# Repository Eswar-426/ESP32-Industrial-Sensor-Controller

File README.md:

# ESP32 Industrial Sensor Controller

A custom, compact PCB designed in **KiCad 10** for an ESP32-based industrial temperature and humidity monitoring system.

The board integrates an **ESP32-WROOM-32** Wi-Fi & Bluetooth microcontroller module, a high-precision **Sensirion SHT31-DIS** digital environmental sensor, and an ultra-low-dropout **AP2112K-3.3** voltage regulator. It features dedicated I²C bus pull-up resistors, hardware Reset and Boot mode tactile switches, comprehensive decoupling networks, and an FTDI-compatible 6-pin UART interface for flashing and serial telemetry.

---

## 3D Board Visualization

<p align="center">
  
  &nbsp;
  
</p>

---

## Features

- **Microcontroller Core:** Espressif ESP32-WROOM-32 dual-core Tensilica Xtensa 32-bit LX6 processor with 2.4 GHz Wi-Fi (802.11 b/g/n) and Bluetooth v4.2 BR/EDR & BLE.
- **Precision Environmental Sensing:** Sensirion SHT31-DIS digital sensor connected via I²C bus (`IO21` SDA, `IO22` SCL) providing ±2% RH accuracy and ±0.2 °C temperature accuracy.
- **Power Management:** AP2112K-3.3 high-current (600 mA), low-noise, ultra-low dropout (LDO) linear regulator delivering stable 3.3 V with dedicated input and output decoupling.
- **Programming & Serial Telemetry:** 6-pin 2.54 mm pitch UART programming header with direct connections to ESP32 UART0 (`TXD0`/`RXD0`), power rails, reset line (`EN`), and boot line (`IO0`).
- **Tactile User Controls:** Dedicated tactile buttons for hardware Reset (`SW1`, EN to GND) and Boot Mode configuration (`SW2`, IO0 to GND) with external 10 kΩ pull-ups.
- **Robust Signal & Power Integrity:** 2-layer PCB stackup with continuous front (F.Cu) and back (B.Cu) ground copper pours, low-inductance thermal via stitching, and dedicated 0603 decoupling capacitors per IC.
- **Antenna Keepout Compliance:** Clean PCB cutout/keepout area maintained around the ESP32 onboard PCB trace antenna to preserve RF performance.

---

## Schematic Overview

*Complete schematic available in vector format: [docs/schematic.pdf](docs/schematic.pdf).*

---

## Bill of Materials (BOM)

| Reference | Value / Part | Package / Footprint | Description | Qty |
| :--- | :--- | :--- | :--- | :---: |
| **U1** | `AP2112K-3.3` | SOT-23-5 | 600 mA Low-Dropout Linear Voltage Regulator (5V to 3.3V) | 1 |
| **U2** | `ESP32-WROOM-32` | SMD-38 (18×25.5 mm) | Espressif Dual-Core Wi-Fi & BLE Microcontroller Module | 1 |
| **U3** | `SHT31-DIS` | DFN-8 (2.5×2.5 mm) | Sensirion High-Precision Digital Humidity & Temperature Sensor | 1 |
| **C1, C2** | `1 µF` | 0603 SMD | Input & Output Filter Capacitors for AP2112K LDO | 2 |
| **C3** | `10 µF` | 0603 SMD | Bulk Decoupling Capacitor for ESP32 3V3 Rail | 1 |
| **C4, C5** | `100 nF` | 0603 SMD | High-Frequency Bypass / Decoupling Capacitors (ESP32 & SHT31) | 2 |
| **R2, R3** | `10 kΩ` | 0603 SMD | Pull-Up Resistors for Boot (`IO0`) and Reset (`EN`) Lines | 2 |
| **R4, R5** | `4.7 kΩ` | 0603 SMD | Dedicated Pull-Up Resistors for I²C Bus (`SDA`, `SCL`) | 2 |
| **SW1, SW2** | `SPST Push Button` | SMD (KMS2xxGP) | Reset (`EN`) and Boot (`IO0`) Control Switches | 2 |
| **J1** | `6-Pin Header (1x06)`| PinHeader 2.54 mm Vertical | UART Interface for Flashing, Debugging & Power Input | 1 |

*Machine-readable CSV format: [docs/bom.csv](docs/bom.csv).*

---

## Pinout & Interface Mapping

### Programming Header (J1)

| Pin | Net Name | Target Device / Pin | Function / Usage |
| :---: | :---: | :---: | :--- |
| **1** | `GND` | System Ground Plane | Common ground connection |
| **2** | `+3.3V` | System 3.3 V Power Rail | 3.3 V supply rail / power monitor |
| **3** | `RXD0` | ESP32 `RXD0` (`GPIO3`) | Serial receive from external USB-UART programmer (TX) |
| **4** | `TXD0` | ESP32 `TXD0` (`GPIO1`) | Serial transmit to external USB-UART programmer (RX) |
| **5** | `EN` | ESP32 `EN` (Chip Enable) | Hardware reset control (active low) |
| **6** | `IO0` | ESP32 `GPIO0` (Boot) | Flashing bootloader entry (pull low during reset) |

### Internal Sensor Bus (I²C)

| Sensor Pin | Net Name | ESP32 Pin | Function |
| :---: | :---: | :---: | :--- |
| **Pin 1 (SDA)** | `IO21` | `GPIO21` | I²C Serial Data (pulled up by R4: 4.7 kΩ to 3.3V) |
| **Pin 4 (SCL)** | `IO22` | `GPIO22` | I²C Serial Clock (pulled up by R5: 4.7 kΩ to 3.3V) |

---

## Design Tools & Verification

### Design Suite
- **KiCad Version:** 10.0.7
- **Schematic Capture:** KiCad Eeschema
- **Layout & Routing:** KiCad PCB Editor
- **Verification Engine:** KiCad Electrical Rules Checker (ERC) & Design Rules Checker (DRC)

### Verification Methodology & Results
- **Schematic ERC:** Passed with **0 errors and 0 warnings**. Power flags, pin types, and hierarchical nets verified. See [docs/erc-report.rpt](docs/erc-report.rpt).
- **PCB DRC:** The report shows zero violations and zero unconnected items under the current project-specific constraints. The settings include a 0.20 mm minimum through-hole drill and a 0.175 mm minimum hole clearance. These settings do not guarantee manufacturer acceptance or fabrication readiness. Review the switch footprint clearances and confirm the design rules with the selected manufacturer before fabrication. See [docs/drc-report.rpt](docs/drc-report.rpt).
- **Copper Architecture:** Solid ground polygon pours on both Top (F.Cu) and Bottom (B.Cu) layers, interconnected with stitching vias for thermal relief and return path continuity.
- **RF Best Practices:** Antenna trace area isolated from underlying copper planes and external routing traces to ensure signal integrity.

> **Verification Scope Notice:**  
> The hardware design has been fully verified using KiCad's Electrical Rules Check (ERC) and PCB Design Rules Check (DRC). Physical board fabrication, component assembly, firmware flashing, and hardware bench testing have not yet been performed. Fabrication constraints must be re-checked against specific manufacturer design capabilities (e.g., JLCPCB, PCBWay) prior to ordering production panels.

---

## Repository Structure

```
ESP32-Industrial-Sensor-Controller/
├── README.md                                      # Project overview, schematics, BOM, and pinout
├── .gitignore                                     # KiCad lock, backup, and local cache filters
├── hardware/
│   ├── ESP32_Industrial_Sensor_Controller.kicad_pro  # KiCad 10 project file
│   ├── ESP32_Industrial_Sensor_Controller.kicad_sch  # Complete schematic file
│   └── ESP32_Industrial_Sensor_Controller.kicad_pcb  # Fully routed PCB layout
└── docs/
    ├── schematic.pdf                              # Printable vector schematic
    ├── schematic.png                              # High-resolution schematic diagram
    ├── pcb-3d.png                                 # High-definition 3D raytraced board render
    ├── pcb-front.png                              # 3D top render
    ├── pcb-back.png                               # 3D bottom render
    ├── bom.csv                                    # Detailed Bill of Materials
    ├── drc-report.rpt                             # KiCad PCB DRC report (0 errors)
    └── erc-report.rpt                             # KiCad Schematic ERC report (0 errors)
```

---

## Future Improvements & Roadmap

- [ ] Order prototype batch from PCB manufacturer (e.g., JLCPCB / PCBWay) with stencil.
- [ ] Surface-mount component soldering & hot-air rework validation.
- [ ] Power supply rail validation under dynamic RF load (3.3 V line ripple and thermal dissipation).
- [ ] ESP-IDF / Arduino C++ firmware development:
  - SHT31 driver implementation with periodic temperature and relative humidity polling.
  - Non-volatile storage (NVS) Wi-Fi credential provisioning.
  - MQTT / HTTP telemetry publishing to cloud/local IoT dashboards (Home Assistant, AWS IoT, or ThingsBoard).
  - ESP32 Deep Sleep power optimization.
- [ ] Enclosure design (3D printed industrial DIN-rail or wall-mount enclosure).

---

## Project Status

**PCB Design Completed** — Prototype fabrication and hardware validation pending.

---

## Author

**Kanchi Eswar Ram kumar** ([@Eswar-426](https://github.com/Eswar-426))  
ECE Undergraduate | Class of 2026  
*Developed as a PCB design and embedded systems portfolio project.*

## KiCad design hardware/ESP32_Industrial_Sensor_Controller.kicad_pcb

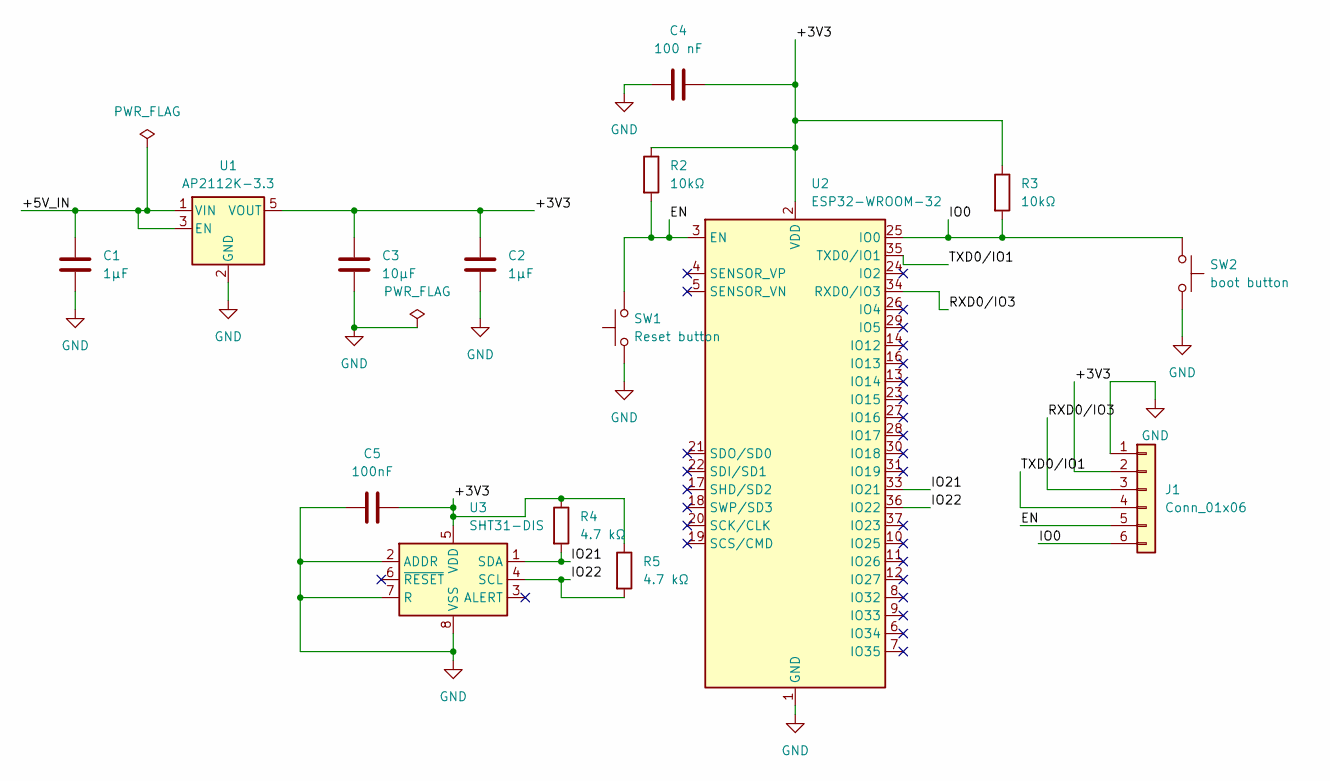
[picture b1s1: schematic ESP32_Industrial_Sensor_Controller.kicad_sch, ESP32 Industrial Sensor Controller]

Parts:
C1, C2: 1µF; C_0603_1608Metric
C3: 10µF; C_0603_1608Metric
C4: 100 nF; C_0603_1608Metric
C5: 100nF; C_0603_1608Metric
J1: Conn_01x06; PinHeader_1x06_P2.54mm_Vertical
R2, R3: 10kΩ; R_0603_1608Metric
R4, R5: 4.7 kΩ; R_0603_1608Metric
SW1: Reset button; SW_SPST_CK_KMS2xxGP
SW2: boot button; SW_SPST_CK_KMS2xxGP
U1: AP2112K-3.3; SOT-23-5
U2: ESP32-WROOM-32
U3: SHT31-DIS; Sensirion_DFN-8-1EP_2.5x2.5mm_P0.5mm_EP1.1x1.7mm

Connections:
/+3V3: C2.1, C3.1, C4.2, C5.2, J1.2, R2.1, R3.1, R4.1, R5.1, U1.5 (VOUT), U2.2 (VDD), U3.5 (VDD)
/+5V_IN: C1.1, U1.1 (VIN), U1.3 (EN)
/EN: J1.5, R2.2, SW1.2, U2.3 (EN)
/IO0: J1.6, R3.2, SW2.1, U2.25 (IO0)
/IO21: R4.2, U2.33 (IO21), U3.1 (SDA)
/IO22: R5.2, U2.36 (IO22), U3.4 (SCL)
/RXD0/IO3: J1.3, U2.34 (RXD0/IO3)
/TXD0/IO1: J1.4, U2.35 (TXD0/IO1)
GND: C1.2, C2.2, C3.2, C4.1, C5.1, J1.1, SW1.1, SW2.2, U1.2 (GND), U2.1 (GND), U2.15 (GND), U2.38 (GND), U2.39 (GND), U3.2 (ADDR), U3.7 (R), U3.8 (VSS), U3.9 (VSS)

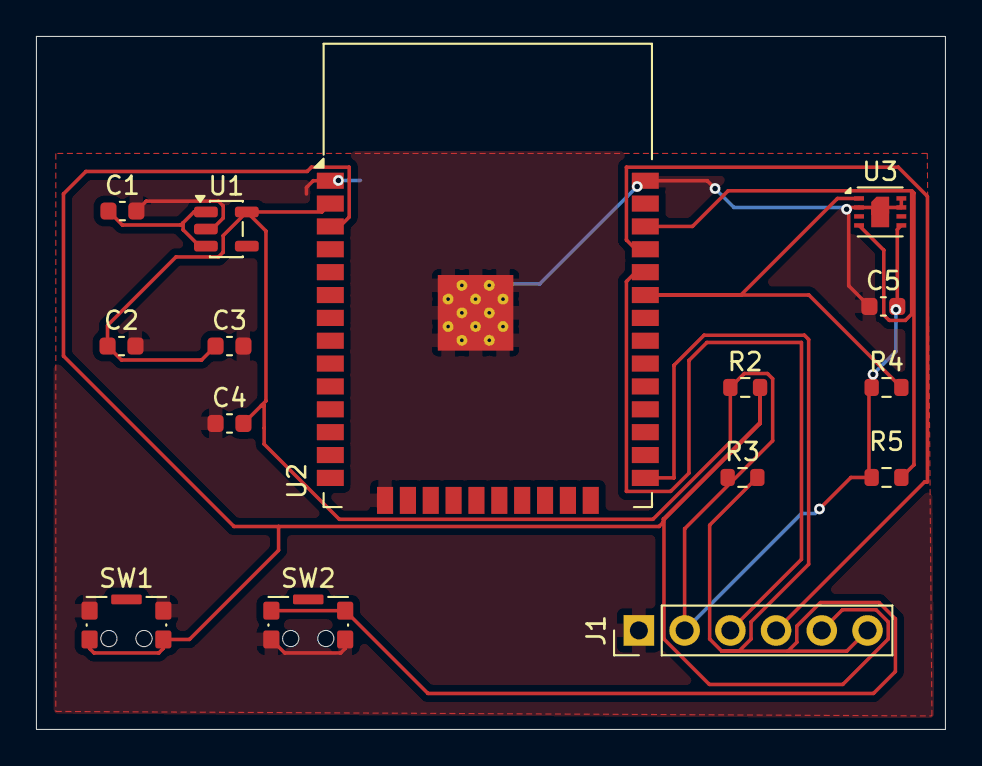
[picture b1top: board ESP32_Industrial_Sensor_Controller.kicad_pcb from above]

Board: 2 copper layers, 50.5 x 38.5 mm, 15 parts (0 on the bottom side), 9 nets.

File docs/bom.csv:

"Reference","Value","Footprint","Description","Quantity"
"C1","1µF","Capacitor_SMD:C_0603_1608Metric","Unpolarized capacitor","1"
"C2","1µF","Capacitor_SMD:C_0603_1608Metric","Unpolarized capacitor","1"
"C3","10µF","Capacitor_SMD:C_0603_1608Metric","Unpolarized capacitor","1"
"C4","100 nF","Capacitor_SMD:C_0603_1608Metric","Unpolarized capacitor","1"
"C5","100nF","Capacitor_SMD:C_0603_1608Metric","Unpolarized capacitor","1"
"J1","Conn_01x06","Connector_PinHeader_2.54mm:PinHeader_1x06_P2.54mm_Vertical","Generic connector, single row, 01x06, script generated (kicad-library-utils/schlib/autogen/connector/)","1"
"R2","10kΩ","Resistor_SMD:R_0603_1608Metric","Resistor","1"
"R3","10kΩ","Resistor_SMD:R_0603_1608Metric","Resistor","1"
"R4","4.7 kΩ","Resistor_SMD:R_0603_1608Metric","Resistor","1"
"R5","4.7 kΩ","Resistor_SMD:R_0603_1608Metric","Resistor","1"
"SW1","Reset button","Button_Switch_SMD:SW_SPST_CK_KMS2xxGP","Push button switch, generic, two pins","1"
"SW2","boot button","Button_Switch_SMD:SW_SPST_CK_KMS2xxGP","Push button switch, generic, two pins","1"
"U1","AP2112K-3.3","Package_TO_SOT_SMD:SOT-23-5","600mA low dropout linear regulator, with enable pin, 3.8V-6V input voltage range, 3.3V fixed positive output, SOT-23-5","1"
"U2","ESP32-WROOM-32","RF_Module:ESP32-WROOM-32","RF Module, ESP32-D0WDQ6 SoC, Wi-Fi 802.11b/g/n, Bluetooth, BLE, 32-bit, 2.7-3.6V, onboard antenna, SMD","1"
"U3","SHT31-DIS","Sensor_Humidity:Sensirion_DFN-8-1EP_2.5x2.5mm_P0.5mm_EP1.1x1.7mm","I²C humidity and temperature sensor, ±2%RH, ±0.2°C, DFN-8","1"
